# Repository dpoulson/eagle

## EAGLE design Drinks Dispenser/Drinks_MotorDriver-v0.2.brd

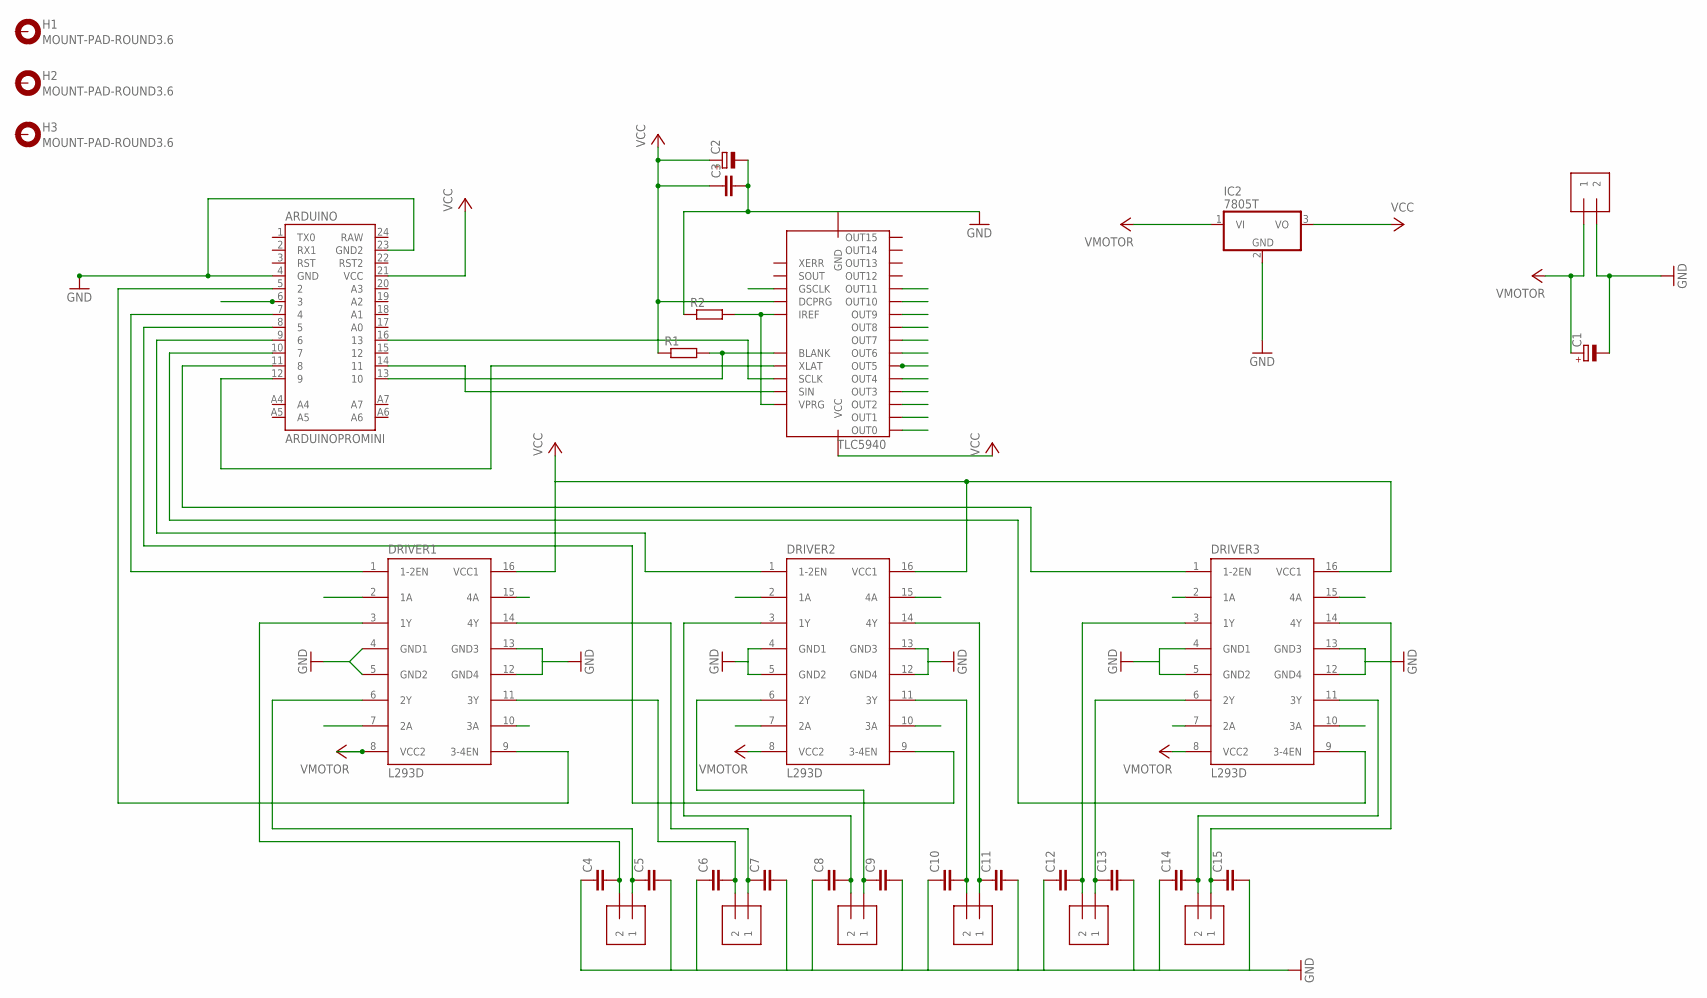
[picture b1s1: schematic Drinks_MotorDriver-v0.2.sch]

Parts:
ARDUINO: ARDUINOPROMINI; ARDUINO_PRO_MINI
C1, C2: CPOL-EUE5-8.5; E5-8,5
C3, C4, C5, C6, C7, C8, C9, C10, C11, C12, C13, C14, C15: C-EU025-025X050; C025-025X050
DRIVER1, DRIVER2, DRIVER3: L293D; DIL16
H1, H2, H3: MOUNT-PAD-ROUND3.6; 3,6-PAD
IC2: 7805T; TO220H
MOT1, MOT2, MOT3, MOT4, MOT5, MOT6: 1X2-3.5MM
R1, R2: R-EU_0204/7; 0204/7
TLC5940: IC-PACKAGE_DIL28-4
VIN: 1X2-3.5MM

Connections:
GND: ARDUINO.4 (GND), ARDUINO.23 (GND2), C1.-, C2.-, C3.2, C4.1, C5.2, C6.1, C7.2, C8.1, C9.2, C10.1, C11.2, C12.1, C13.2, C14.1, C15.2, DRIVER1.4 (GND1), DRIVER1.5 (GND2), DRIVER1.12 (GND4), DRIVER1.13 (GND3), DRIVER2.4 (GND1), DRIVER2.5 (GND2), DRIVER2.12 (GND4), DRIVER2.13 (GND3), DRIVER3.4 (GND1), DRIVER3.5 (GND2), DRIVER3.12 (GND4), DRIVER3.13 (GND3), IC2.2 (GND), R2.1, TLC5940.22 (GND), VIN.2
GSCLK: ARDUINO.6 (3), TLC5940.18 (GSCLK)
MOT1A: DRIVER1.2 (1A), TLC5940.28 (OUT0)
MOT1B: DRIVER1.7 (2A), TLC5940.1 (OUT1)
MOT2A: DRIVER1.10 (3A), TLC5940.2 (OUT2)
MOT2B: DRIVER1.15 (4A), TLC5940.3 (OUT3)
MOT3A: DRIVER2.2 (1A), TLC5940.4 (OUT4)
MOT3B: DRIVER2.7 (2A), TLC5940.5 (OUT5)
MOT4A: DRIVER2.10 (3A), TLC5940.6 (OUT6)
MOT4B: DRIVER2.15 (4A), TLC5940.7 (OUT7)
MOT5A: DRIVER3.2 (1A), TLC5940.8 (OUT8)
MOT5B: DRIVER3.7 (2A), TLC5940.9 (OUT9)
MOT6A: DRIVER3.10 (3A), TLC5940.10 (OUT10)
MOT6B: DRIVER3.15 (4A), TLC5940.11 (OUT11)
unnamed: ARDUINO.13 (10), R1.2, TLC5940.23 (BLANK)
unnamed: R2.2, TLC5940.20 (IREF), TLC5940.27 (VPRG)
unnamed: ARDUINO.14 (11), TLC5940.26 (SIN)
unnamed: ARDUINO.12 (9), TLC5940.24 (XLAT)
unnamed: ARDUINO.5 (2), DRIVER1.9 (3-4EN)
unnamed: ARDUINO.7 (4), DRIVER1.1 (1-2EN)
unnamed: ARDUINO.8 (5), DRIVER2.9 (3-4EN)
unnamed: ARDUINO.9 (6), DRIVER2.1 (1-2EN)
unnamed: ARDUINO.10 (7), DRIVER3.9 (3-4EN)
unnamed: ARDUINO.11 (8), DRIVER3.1 (1-2EN)
unnamed: C4.2, DRIVER1.3 (1Y), MOT1.2
unnamed: C5.1, DRIVER1.6 (2Y), MOT1.1
unnamed: C7.1, DRIVER1.14 (4Y), MOT2.1
unnamed: C6.2, DRIVER1.11 (3Y), MOT2.2
unnamed: C8.2, DRIVER2.3 (1Y), MOT3.2
unnamed: C9.1, DRIVER2.6 (2Y), MOT3.1
unnamed: C10.2, DRIVER2.11 (3Y), MOT4.2
unnamed: C11.1, DRIVER2.14 (4Y), MOT4.1
unnamed: C12.2, DRIVER3.3 (1Y), MOT5.2
unnamed: C13.1, DRIVER3.6 (2Y), MOT5.1
unnamed: C14.2, DRIVER3.11 (3Y), MOT6.2
unnamed: C15.1, DRIVER3.14 (4Y), MOT6.1
SCLK: ARDUINO.16 (13), TLC5940.25 (SCLK)
VCC: ARDUINO.21 (VCC), C2.+, C3.1, DRIVER1.16 (VCC1), DRIVER2.16 (VCC1), DRIVER3.16 (VCC1), IC2.3 (VO), R1.1, TLC5940.19 (DCPRG), TLC5940.21 (VCC)
VMOTOR: C1.+, DRIVER1.8 (VCC2), DRIVER2.8 (VCC2), DRIVER3.8 (VCC2), IC2.1 (VI), VIN.1

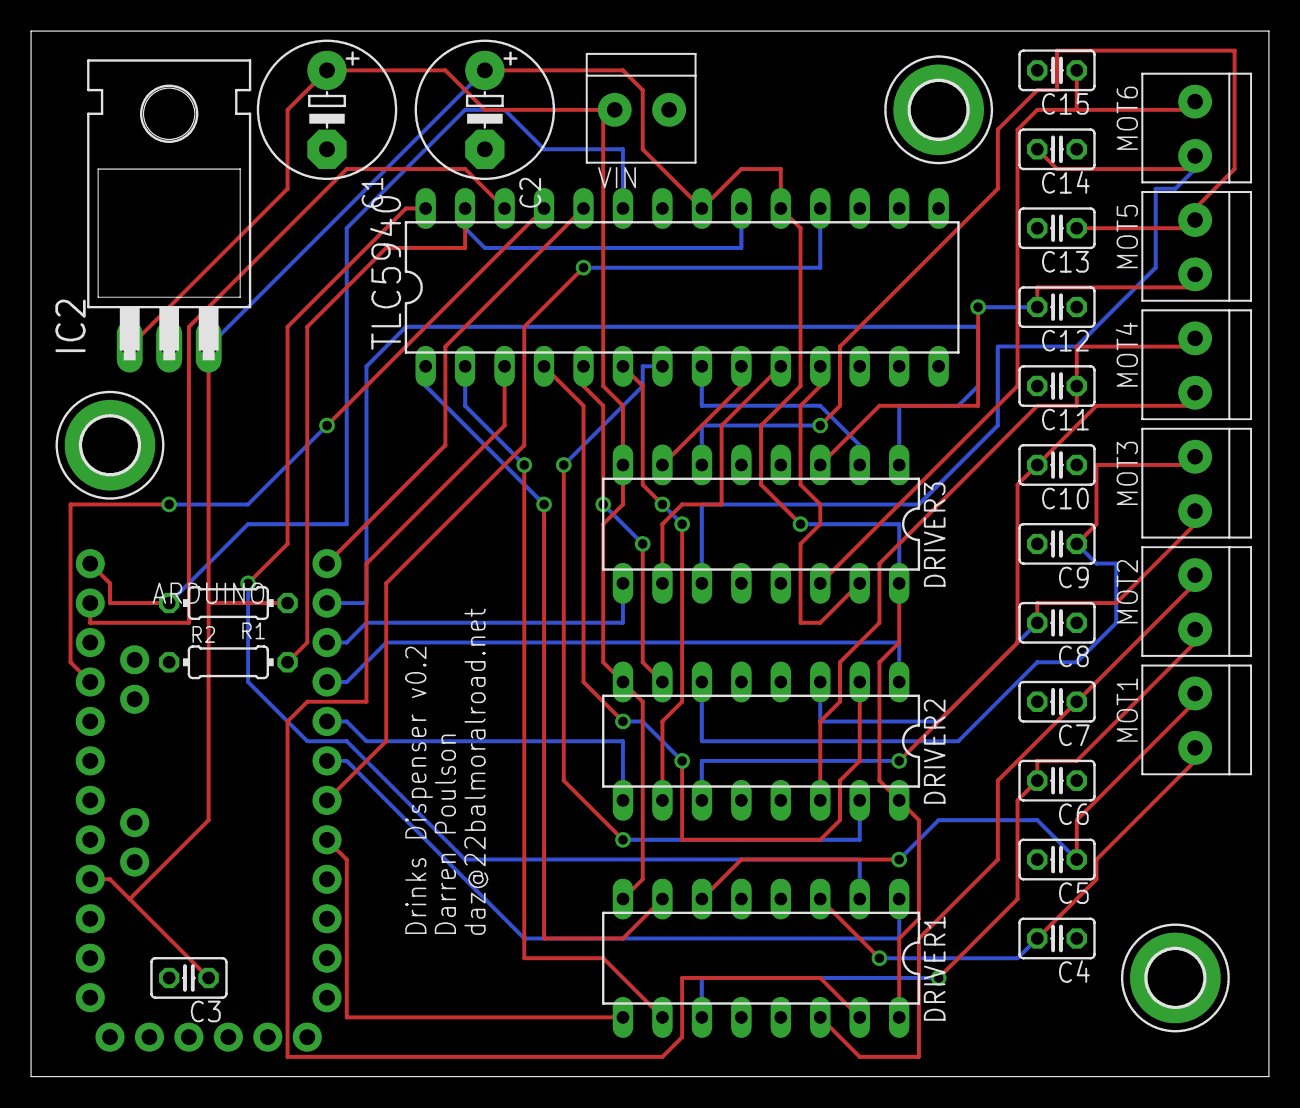
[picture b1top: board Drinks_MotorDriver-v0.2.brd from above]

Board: 2 copper layers, 79.7 x 67.3 mm, 33 parts (0 on the bottom side), 39 nets.

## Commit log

2014-01-21 Initial import

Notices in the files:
parts and their libraries:
SparkFun-Boards: Licensing: CC v3.0 Share-Alike You are welcome to use this library for commercial purposes.
